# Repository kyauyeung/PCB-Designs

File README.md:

These are early schematic and PCB designs for my first functioning PCB projects. The first project is a very simple model and the second is fit to serve a temperature sensor.

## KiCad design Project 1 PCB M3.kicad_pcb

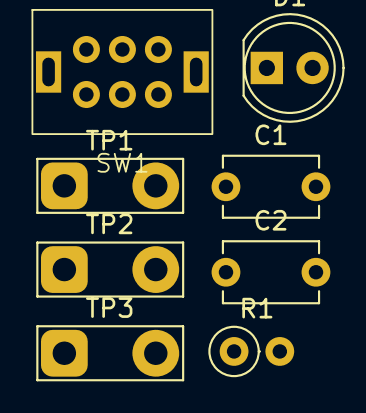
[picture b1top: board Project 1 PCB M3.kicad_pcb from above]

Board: 2 copper layers, 8 parts (0 on the bottom side), 6 nets, no tracks yet.

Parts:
C1, C2: C; C_Disc_D5.1mm_W3.2mm_P5.00mm
D1: LED; LED_D5.0mm
R1: R; R_Axial_DIN0207_L6.3mm_D2.5mm_P2.54mm_Vertical
SW1: PWR_SW; SLW-826947-5A-RA-D
TP1, TP2, TP3: TestPoint_2Pole; TestPoint_2Pads_Pitch5.08mm_Drill1.3mm

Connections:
+5C: C2.1, R1.1, TP3.2
GND: C1.2, C2.2, D1.1 (K), TP1.1, TP3.1
unnamed: D1.2 (A), R1.2
unnamed: SW1.2, TP1.2
unnamed: SW1.3, TP2.1
unnamed: C1.1, SW1.1, TP2.2

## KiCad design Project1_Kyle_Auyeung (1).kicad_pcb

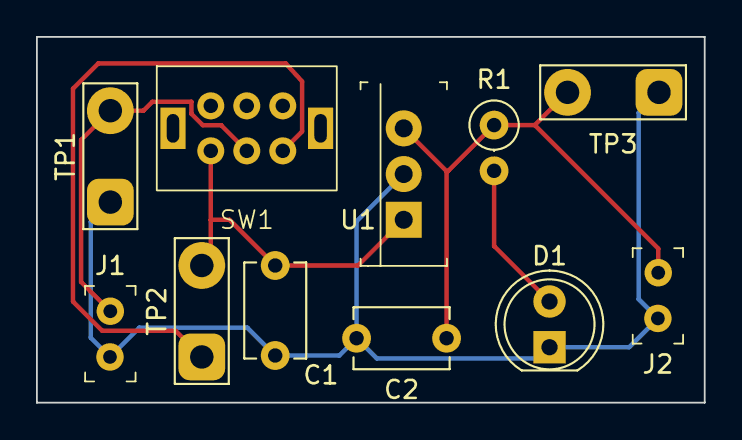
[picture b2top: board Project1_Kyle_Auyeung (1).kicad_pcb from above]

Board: 2 copper layers, 37.1 x 20.3 mm, 11 parts (0 on the bottom side), 6 nets.

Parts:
C1: 0.22u; C_Disc_D5.1mm_W3.2mm_P5.00mm
C2: 0.1uF; C_Disc_D5.1mm_W3.2mm_P5.00mm
D1: Red; LED_D5.0mm
J1: Vin; PinHeader_1x2_P2.54mm
J2: 5V; PinHeader_1x2_P2.54mm
R1: 1.0k; R_Axial_DIN0207_L6.3mm_D2.5mm_P2.54mm_Vertical
SW1: PWR_SW; SLW-826947-5A-RA-D
TP1: Vin; TestPoint_2Pads_Pitch5.08mm_Drill1.3mm
TP2: I_in; TestPoint_2Pads_Pitch5.08mm_Drill1.3mm
TP3: 5V; TestPoint_2Pads_Pitch5.08mm_Drill1.3mm
U1: L7805CV; TO-220-3

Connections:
+5C: C2.1, J2.2, R1.1, TP3.2, U1.3 (OUT)
GND: C1.2, C2.2, D1.1 (K), J1.2, J2.1, TP1.1, TP3.1, U1.2 (GND)
unnamed: D1.2 (A), R1.2
unnamed: J1.1, SW1.2, TP1.2
unnamed: SW1.3, TP2.1
unnamed: C1.1, SW1.1, TP2.2, U1.1 (IN)

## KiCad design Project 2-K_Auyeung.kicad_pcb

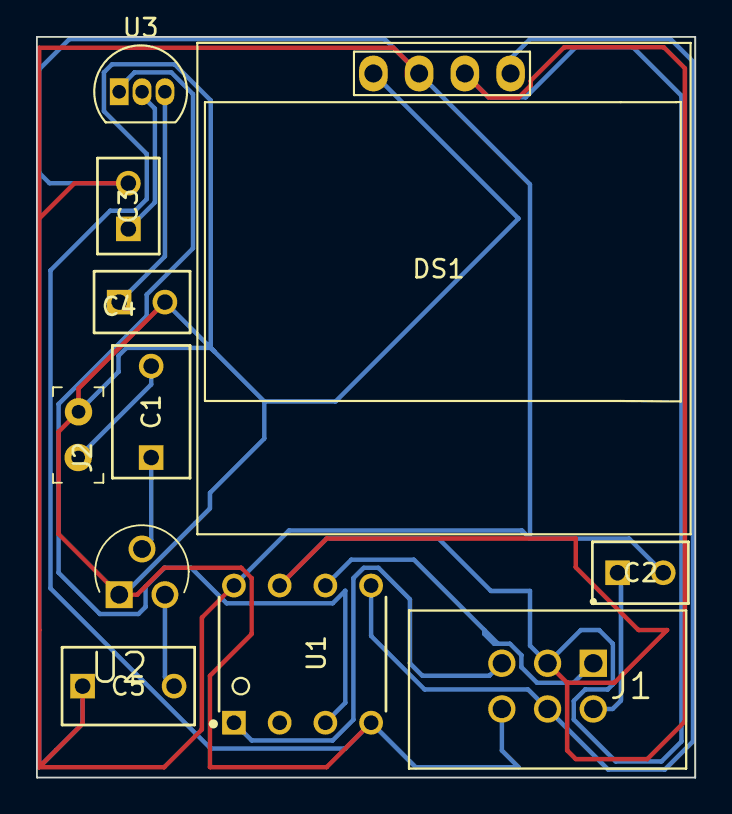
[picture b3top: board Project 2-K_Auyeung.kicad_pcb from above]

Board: 2 copper layers, 36.6 x 41.1 mm, 11 parts (0 on the bottom side), 13 nets.

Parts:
C1: Capacitor1; C330C105K5R5TA
C2: Capacitor2; C320C104K5R5TA7317
C3: Capacitor3; C320C104K5R5TA7317
C4: C4; C320C104K5R5TA7317
C5: Capacitor5; C330C105K5R5TA
DS1: OLDED display; SSD1306
J1: Socket; 30306-6002HB
J2: Pin header; PinHeader_1x2_P2.54mm
U1: ATTINY85-20PU
U2: VRegulator; MCP1700-3302E_TO
U3: TMP sensor; TO-92L_Inline

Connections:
+3.3V: C2.2, C3.2, C5.1, DS1.2 (VCC), U1.8 (VCC)
GND: C4.2, DS1.1 (GND), J1.6, J2.2, U1.4 (GND), U2.1 (GND)
unnamed: C1.2, J2.1
unnamed: C2.1, J1.2
unnamed: J1.1, U1.6 (PB1)
unnamed: U1.3 (PB4), U3.1 (~RESET)
unnamed: C1.1, U2.2 (VIN)
unnamed: C5.2, U2.3 (VOUT)
unnamed: C4.1, U3.3 (GND)
unnamed: C3.1, U3.2 (IN)
RST: J1.5, U1.1 (PB5)
SCL: DS1.3 (SCL), J1.3, U1.7 (PB2)
SDA: DS1.4 (SDA), J1.4, U1.5 (PB0)

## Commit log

2024-05-31 Add files via upload
    Video demonstrations of functioning 1st PCB design
